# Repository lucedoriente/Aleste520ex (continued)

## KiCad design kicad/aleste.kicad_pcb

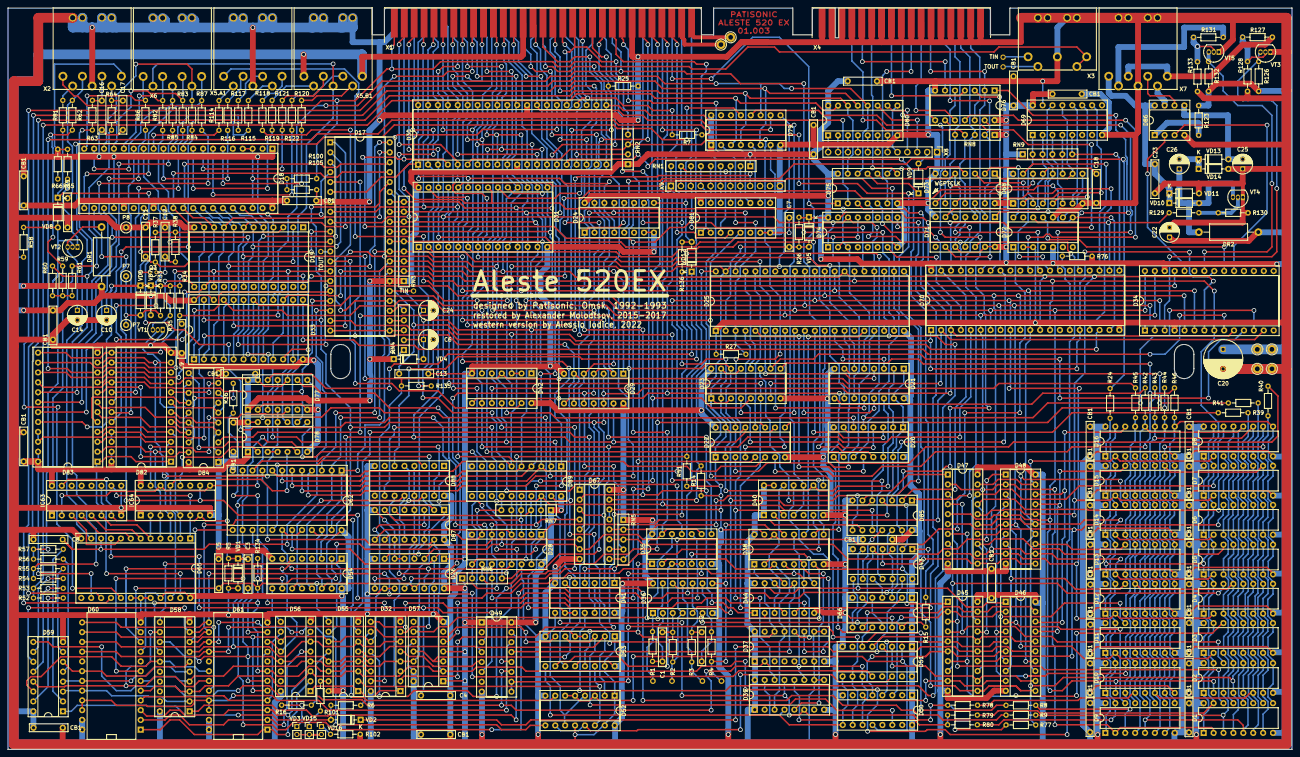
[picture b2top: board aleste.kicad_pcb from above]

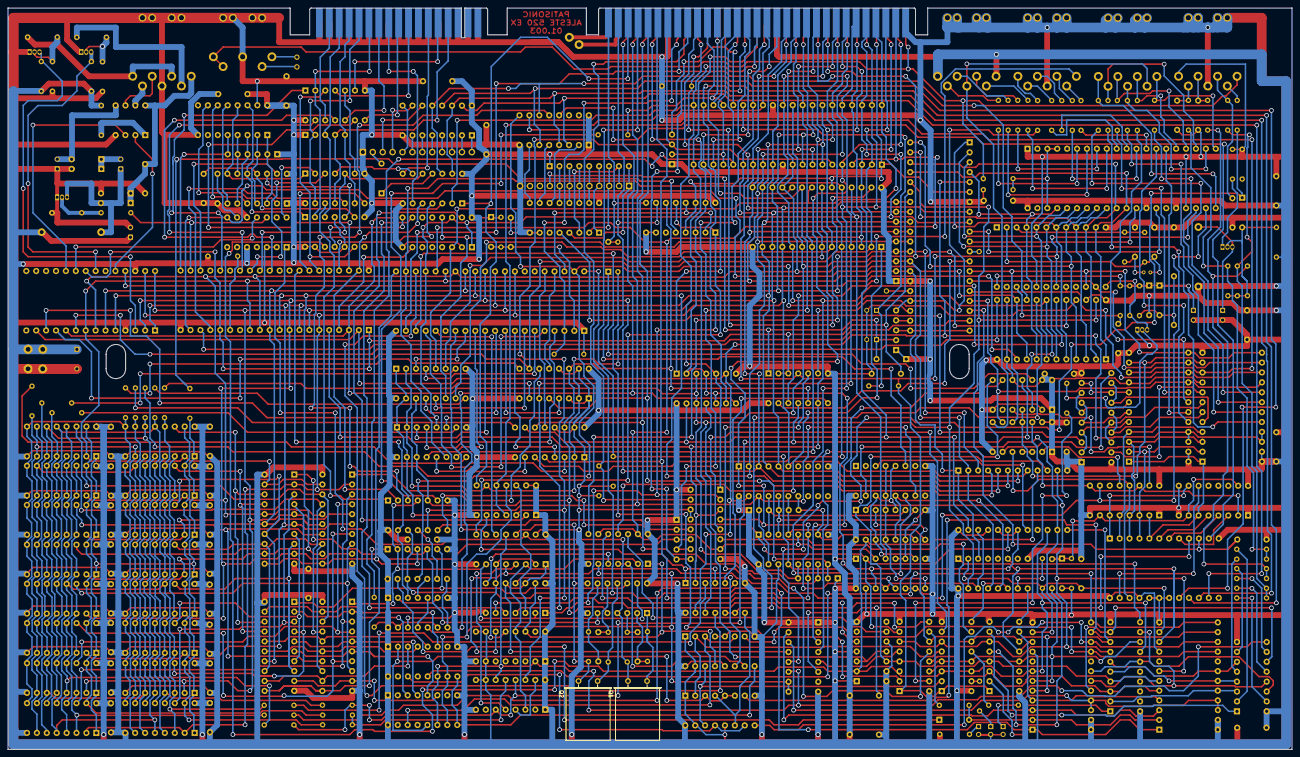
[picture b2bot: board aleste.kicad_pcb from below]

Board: 2 copper layers, 329.2 x 190.1 mm, 279 parts (2 on the bottom side), 452 nets.

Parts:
C1, C2: 470; C_Disc_D7.5_P2.5
C3, C4, C5, C15, C16, C17, C18: CAP; C_Disc_D7.5_P2.5
C6, C24: 1мк; C_Radial_D5_L6_P2.5
C7: 0,33мк; C_Disc_D7.5_P2.5
C8: 1н; C_Disc_D7.5_P2.5
C9: 1,5мк; C_Disc_D7.5_P2.5
C10, C14, C22: 100мк; C_Radial_D5_L6_P2.5
C11: 12; C_Disc_D7.5_P2.5
C12: 24; C_Disc_D7.5_P2.5
C13: 47н; C_Disc_D7.5_P2.5
C20: 1000мк; C_Radial_D10_L16_P5
C23: 0,47мк; C_Disc_D7.5_P2.5
C25, C26: 47мк; C_Radial_D5_L6_P2.5
CB1, CB1#2, CB1#3, CB1#4, CB1#5, CB1#6, CB1#7, CB1#8, CB1#9, CB1#10, CB1#11, CB1#12, CB1#13, CB1#14, CB1#15, CB1#16, CB1#17, CB1#18, CB1#19, CB1#20, CB1#21, CB1#22, CB1#23, CB1#24, CB1#25, CB1#26, CB1#27, CB1#28, CB1#29, CB1#30: 0,1мк; C_Disc_D7.5_P2.5
D1, D2, D3, D4, D5, D6, D7, D8, D9, D10, D11, D12, D13, D14, D15, D16: HM50256P-20; DIP-16_W7.62mm
D17: 8255; DIP-40_W15.24mm_Socket
D18: AY-3-8910; DIP-40_W15.24mm_Socket
D19: MC146818; DIP-24_W15.24mm_Socket
D20, D21, D22, D23, D52, D53: 74LS153; DIP-16_W7.62mm_Socket
D24, D81: 74LS151; DIP-16_W7.62mm_Socket
D25: MC6845P; DIP-40_W15.24mm_Socket
D26: 74LS253; DIP-16_W7.62mm_Socket
D28, D67: AM27S20; DIP-16_W7.62mm_Socket
D29, D44: 74LS32; DIP-14_W7.62mm_Socket
D30: Z80; DIP-40_W15.24mm_Socket
D31: 27512; DIP-28_W15.24mm_Socket
D32, D55, D56, D59, D68, D79: 74LS174; DIP-16_W7.62mm_Socket
D33: 8253; DIP-24_W15.24mm_Socket
D34: 8251A; DIP-28_W15.24mm_Socket
D35, D85: 74LS08; DIP-14_W7.62mm_Socket
D36, D42, D73: 74LS04; DIP-14_W7.62mm_Socket
D37: 74LS161; DIP-16_W7.62mm_Socket
D38: 74LS257; DIP-16_W7.62mm_Socket
D39, D49, D50, D51: 74LS194; DIP-16_W7.62mm_Socket
D40, D57, D66, D71, D77: 74LS74; DIP-14_W7.62mm_Socket
D41, D75, D78: 74LS00; DIP-14_W7.62mm_Socket
D43: 74LS33; DIP-14_W7.62mm_Socket
D45, D46, D47, D48: 74LS373; DIP-20_W7.62mm_Socket
D54, D74: 74LS155; DIP-16_W7.62mm_Socket
D58, D84: 74LS374; DIP-20_W7.62mm_Socket
D60, D61: 1802ИР1; DIP-24
D62, D65: 2716; DIP-24_W15.24mm_Socket
D69: 27S18; DIP-16_W7.62mm_Socket
D70: UPD765AC; DIP-40_W15.24mm_Socket
D72: 74LS93; DIP-14_W7.62mm_Socket
D76: 74LS05; DIP-14_W7.62mm_Socket
D80: 74LS145; DIP-16_W7.62mm_Socket
D82, D83: 1802ИР1; DIP-24_W15.24mm_Socket
D86: SN75150; DIP-8_W7.62mm_Socket
D87, D88: 74LS170; DIP-16_W7.62mm_Socket
D89: 74LS245; DIP-20_W7.62mm_Socket
DR1: 91мкГ; L_Axial_L9.5mm_D4.0mm_P15.24mm_Horizontal_Fastron_SMCC
DR2: 51мкГ; L_Axial_L9.5mm_D4.0mm_P15.24mm_Horizontal_Fastron_SMCC
IC63, IC64: MC14520BDP; DIP-16_W7.62mm_Socket
P1, P2, P3, P4, P5, P6, P7, P7#2, P8: PIN
Q1: 16 MHz; Crystal_HC49-U_Horizontal
Q2: 13.333 MHz; Crystal_HC49-U_Horizontal
Q3: QUARTZ; Crystal_DS15_D1.5mm_L5.0mm_Vertical
R1, R2, R3, R4, R36, R51, R60, R100, R105: 1,2к; R_Axial_DIN0204_L3.6mm_D1.6mm_P7.62mm_Horizontal
R5, R6, R14, R15, R25, R76, R82, R83, R84, R85, R86, R87, R123, R126, R132: 2,7к; R_Axial_DIN0204_L3.6mm_D1.6mm_P7.62mm_Horizontal
R7, R8, R9, R24, R39, R40, R41, R42, R43, R44, R45, R46, R77, R78, R79, R80: 51; R_Axial_DIN0204_L3.6mm_D1.6mm_P7.62mm_Horizontal
R16, R53, R55, R57, R101, R102, R134: 360; R_Axial_DIN0204_L3.6mm_D1.6mm_P7.62mm_Horizontal
R26, R34: 10k; R_Axial_DIN0204_L3.6mm_D1.6mm_P7.62mm_Horizontal
R27, R33, R135: 10к; R_Axial_DIN0204_L3.6mm_D1.6mm_P7.62mm_Horizontal
R35: 390к; R_Axial_DIN0204_L3.6mm_D1.6mm_P7.62mm_Horizontal
R37: 10М; R_Axial_DIN0204_L3.6mm_D1.6mm_P7.62mm_Horizontal
R38: 470к; R_Axial_DIN0204_L3.6mm_D1.6mm_P7.62mm_Horizontal
R52, R54, R56: 200; R_Axial_DIN0204_L3.6mm_D1.6mm_P7.62mm_Horizontal
R58, R129: 510; R_Axial_DIN0204_L3.6mm_D1.6mm_P7.62mm_Horizontal
R59, R127, R131: 6,8к; R_Axial_DIN0204_L3.6mm_D1.6mm_P7.62mm_Horizontal
R61, R128, R133: 3,3к; R_Axial_DIN0204_L3.6mm_D1.6mm_P7.62mm_Horizontal
R62, R63, R64, R66, R81, R130: 220; R_Axial_DIN0204_L3.6mm_D1.6mm_P7.62mm_Horizontal
R65: 120; R_Axial_DIN0204_L3.6mm_D1.6mm_P7.62mm_Horizontal
R114, R115, R116, R117, R118, R119, R120, R121, R122: 27; R_Axial_DIN0204_L3.6mm_D1.6mm_P7.62mm_Horizontal
R136: RES; R_Axial_DIN0204_L3.6mm_D1.6mm_P7.62mm_Horizontal
RN1, RN3: 10k; R_Array_SIP9
RN2: 10k; R_Array_SIP4
RN4: 10k; R_Array_SIP5
RN5, RN6: 1.2k; R_Array_SIP5
RN7, RN9: 1.2k; R_Array_SIP6
RN8: 2,7k; R_Array_SIP5
VD1, VD2, VD4, VD5, VD6, VD7, VD8, VD9, VD10, VD12, VD13, VD14: Diode; D_DO-35_SOD27_P7.62mm_Horizontal
VD3: DA; PinHeader_1x02_P2.00mm_Vertical
VD11: ZDiode; D_DO-35_SOD27_P7.62mm_Horizontal
VD15: CAPS; PinHeader_1x02_P2.00mm_Vertical
VD16: PWR; PinHeader_1x02_P2.00mm_Vertical
VT1, VT2, VT3, VT4, VT5: NPN; TO-92_Inline
X1: SLOT-62; SLOT_62
X2, X5.A1, X5.B1, X6, X7: CONN-7S; DNR-8F1R
X3: CONN-5S; DNR-5F1R
X4: SLOT-34
X8, X9: CONN-12; PinHeader_1x12_P2.54mm_Vertical

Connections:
/1CY: D78.2, IC64.12 (Q1B)
/1M: D18.22 (CLOCK), D37.11 (Q3), D38.5 (I0b), IC64.10 (EB)
/2CY: D65.22 (A9), D78.5, IC64.13 (Q2B)
/2M: D37.12 (Q2), D38.2 (I0a), D38.6 (I1b), D44.9
/3CY: D78.12, IC63.2 (EA), IC64.9 (CB), IC64.14 (Q3B)
/4M: D35.2, D37.13 (Q1), D38.3 (I1a), D39.3 (P0)
/8M: D35.1, D37.14 (Q0), D44.13, D53.13 (I3b)
/16MHZ: D36.4, D38.14 (I0c), D72.1 (CP1..3), Q1.1, R2.2
/A0: D30.30 (A0), D31.10 (A0), D33.19 (A0), D41.2, D42.9, D67.3 (A4), D70.5 (A0), X1.B9
/A1: D20.6 (I0a), D30.31 (A1), D31.9 (A1), D33.20 (A1), X1.A9
/A2: D20.10 (I0b), D30.32 (A2), D31.8 (A2), X1.B8
/A3: D21.6 (I0a), D30.33 (A3), D31.7 (A3), X1.A8
/A4: D21.10 (I0b), D30.34 (A4), D31.6 (A4), X1.B7
/A5: D22.6 (I0a), D30.35 (A5), D31.5 (A5), X1.A7
/A6: D23.6 (I0a), D30.36 (A6), D31.4 (A6), D44.4, X1.B6
/A7: D21.11 (I1b), D30.37 (A7), D31.3 (A7), D74.13 (A0), X1.A6
/A8: D17.9 (A0), D20.5 (I1a), D25.24 (RS), D26.4 (I2a), D30.38 (A8), D31.25 (A8), D34.12 (C/D), D74.1 (Ea1), D74.14 (Eb1), X1.B5
/A9: D17.8 (A1), D20.11 (I1b), D25.22 (R/~W), D26.12 (I2b), D30.39 (A9), D31.24 (A9), X1.A5
/A10: D21.5 (I1a), D30.40 (A10), D31.21 (A10), D74.3 (A1), X1.B4
/A11: D17.6 (~CS), D24.4 (I0), D24.14 (I5), D30.1 (A11), D31.23 (A11), X1.A4
/A12: D23.10 (I0b), D30.2 (A12), D31.2 (A12), D34.11 (CS), X1.B3
/A13: D22.10 (I0b), D29.13, D30.3 (A13), D31.26 (A13), D62.23 (A8), X1.A3
/A14: D25.25 (~CS), D26.3 (I3a), D28.5 (A0), D30.4 (A14), D35.9, D35.13, D67.7 (A2), X1.B2
/A15: D26.13 (I3b), D28.6 (A1), D30.5 (A15), D54.14 (Eb1), D62.22 (A9), D67.4 (A3), D89.1 (A->B), X1.A2
/AGND: P4.1, X1.A30
/AVCC: P3.1, X1.A31
/BUFFER0: D47.1 (OE), D67.12 (O0), RN5.2 (R1.2)
/BUFFER1: D48.1 (OE), D67.11 (O1), RN5.3 (R2.2)
/CAS: D39.12 (Q3), R79.1, R80.1
/CBUF: D25.21 (CLK), D43.4, D47.11 (LE), D48.11 (LE)
/CLK: D30.6 (~CLK), D39.14 (Q1), D40.3 (C), RN2.3 (R2), X1.B25
/CPU/LOP: D43.10, D66.4 (~S)
/CPU/~RESET*: C24.1, D30.26 (~RESET), R135.2
/CS53: D32.12 (Q4), D42.5
/CURSOR: D25.19 (CURSOR), D33.16 (G2), X1.B23
/Clocks & CRTC/13MHZ: D36.8, D38.13 (I1c), Q2.1, R4.2
/Clocks & CRTC/V11: D25.14 (MA10), D38.10 (I1d)
/Clocks & CRTC/V13: D25.16 (MA12), D38.11 (I0d)
/Clocks & CRTC/~RESET2: C7.2, D25.2 (~RESET), R26.1, VD5.2 (A)
/D0: D1.2 (DIN), D9.2 (DIN), D17.34 (D0), D25.33 (D0), D30.14 (D0), D31.11 (D0), D34.27 (D0), D47.2 (O0), D48.2 (O0), D62.8 (A0), D70.6 (DB0), D89.6 (A4), RN3.9 (R8), X1.B13
/D1: D2.2 (DIN), D10.2 (DIN), D17.33 (D1), D25.32 (D1), D30.15 (D1), D31.12 (D1), D34.28 (D1), D47.5 (O1), D48.5 (O1), D62.7 (A1), D70.7 (DB1), D89.5 (A3), RN3.8 (R7), X1.A13
/D2: D3.2 (DIN), D11.2 (DIN), D17.32 (D2), D25.31 (D2), D30.12 (D2), D31.13 (D2), D34.1 (D2), D47.6 (O2), D48.6 (O2), D62.6 (A2), D70.8 (DB2), D89.4 (A2), RN3.7 (R6), X1.B12
/D3: D4.2 (DIN), D12.2 (DIN), D17.31 (D3), D25.30 (D3), D30.8 (D3), D31.15 (D3), D34.2 (D3), D47.9 (O3), D48.9 (O3), D62.5 (A3), D70.9 (DB3), D89.3 (A1), RN3.6 (R5), X1.A12
/D4: D5.2 (DIN), D13.2 (DIN), D17.30 (D4), D25.29 (D4), D30.7 (D4), D31.16 (D4), D34.5 (D4), D47.12 (O4), D48.12 (O4), D62.4 (A4), D70.10 (DB4), D89.2 (A0), RN3.5 (R4), X1.B11
/D5: D6.2 (DIN), D14.2 (DIN), D17.29 (D5), D25.28 (D5), D30.9 (D5), D31.17 (D5), D34.6 (D5), D47.15 (O5), D48.15 (O5), D62.3 (A5), D70.11 (DB5), RN3.4 (R3), X1.A11
/D6: D7.2 (DIN), D15.2 (DIN), D17.28 (D6), D25.27 (D6), D30.10 (D6), D31.18 (D6), D34.7 (D6), D47.16 (O6), D48.16 (O6), D54.13 (A0), D62.2 (A6), D70.12 (DB6), RN3.3 (R2), X1.B10
/D7: D8.2 (DIN), D16.2 (DIN), D17.27 (D7), D25.26 (D7), D30.13 (D7), D31.19 (D7), D34.8 (D7), D47.19 (O7), D48.19 (O7), D54.3 (A1), D62.1 (A7), D70.13 (DB7), RN3.2 (R1), X1.A10
/DEN: D25.18 (DE), D77.12 (D)
/DIS: D20.2 (S1), D21.2 (S1), D22.2 (S1), D23.2 (S1), D24.10 (S1), D40.9 (Q), X1.B30
/DISCINT: D17.19 (PB1), D70.18 (INT)
/DW: D70.22 (RDW), D72.12 (Q0), R129.1
/EXRG: D44.5, D74.10 (Q1b)
/FDC/DSKRDY: D70.35 (RDY), D71.9 (Q), D76.3
/FDC/FP0: D68.3 (D0), D69.1 (Q0), RN9.2 (R1)
/FDC/FP1: D68.4 (D1), D69.2 (Q1), RN9.3 (R2)
/FDC/FP2: D68.6 (D2), D69.3 (Q2), RN9.4 (R3)
/FDC/FP3: D68.11 (D3), D69.4 (Q3), RN9.5 (R4)
/FDC/RDD: D68.15 (Q5), D70.23 (RD)
/FDC/RW/S: D70.39 (~RW/SEEK), D75.5, D85.2
/FDC/WRC: D69.5 (Q4), D70.21 (WCK), RN9.6 (R5)
/FDC/~DIR: D76.8, X4.A9
/FDC/~DRIVE0: D76.6, X4.A5
/FDC/~DRIVE1: D75.8, X4.A6
/FDC/~GATE: D71.2 (D), D76.2, X4.A12
/FDC/~INDEX: D73.11, RN8.4 (R3.2), X4.A4
/FDC/~MOTOR: D76.4, X4.A8
/FDC/~RDATA: D71.3 (C), RN8.3 (R2.2), X4.A15
/FDC/~SIDE: D76.12, X4.A16
/FDC/~STEP: D75.6, X4.A10
/FDC/~TRAC0: D73.13, RN8.2 (R1.2), X4.A13
/FDC/~WRDAT: D76.10, X4.A11
/FDC/~WRTPRT: D73.9, RN8.5 (R4.2), X4.A14
/Gate Array/4ST: D35.3, D35.4, D53.10 (I0b)
/Gate Array/8ST: D44.11, D53.11 (I1b)
/Gate Array/"A": D26.7 (Za), D87.5 (Ra), D87.14 (Wa), D88.5 (Ra), D88.14 (Wa)
/Gate Array/"B": D26.9 (Zb), D87.4 (Rb), D87.13 (Wb), D88.4 (Rb), D88.13 (Wb)
/Gate Array/B: C15.1, R62.1, X2.4
/Gate Array/BLAKS: D32.10 (Q3), R6.2
/Gate Array/BLANK: D59.1 (~Mr), R6.1, VD2.2 (A)
/Gate Array/C0: D58.2 (O0), D59.3 (D0), D60.20 (DB0)
/Gate Array/C1: D58.5 (O1), D59.4 (D1), D60.19 (DB1)
/Gate Array/C2: D58.6 (O2), D59.6 (D2), D60.18 (DB2)
/Gate Array/C3: D58.9 (O3), D59.11 (D3), D61.20 (DB0)
/Gate Array/C4: D58.12 (O4), D59.13 (D4), D61.19 (DB1)
/Gate Array/C5: D58.15 (O5), D59.14 (D5), D61.18 (DB2)
/Gate Array/CBORDER: D54.6 (Q1a), D58.11 (Cp)
/Gate Array/COLOR: C5.2, D54.2 (Ea2), D60.11 (~WA), D61.11 (~WA), R134.1
/Gate Array/G: C16.1, R63.1, X2.5
/Gate Array/HIGHTX: D32.5 (Q1), D49.5 (P2)
/Gate Array/HIGHTY: D32.2 (Q0), R136.2
/Gate Array/LED0: D55.12 (Q4), R16.1
/Gate Array/LED1: D55.15 (Q5), R101.1
/Gate Array/M0: D28.7 (A2), D87.10 (Q1), D89.14 (B4), RN7.6 (R5.2)
/Gate Array/M1: D28.4 (A3), D87.9 (Q2), D89.15 (B3), RN7.5 (R4.2)
/Gate Array/M2: D28.3 (A4), D87.7 (Q3), D89.16 (B2), RN7.4 (R3.2)
/Gate Array/M3: D28.2 (A5), D87.6 (Q4), D89.17 (B1), RN7.3 (R2.2)
/Gate Array/MAPER: D54.12 (Q3b), D87.12 (~Ew), D88.12 (~Ew)
/Gate Array/MAPMOD: D26.2 (A1), D28.1 (A6), D32.7 (Q2), D62.19 (A10), D85.9
/Gate Array/MODE: D54.11 (Q2b), D55.9 (Cp)
/Gate Array/MODE0: D52.14 (S0), D53.14 (S0), D55.2 (Q0)
/Gate Array/MODE1: D52.2 (S1), D53.2 (S1), D55.5 (Q1)
/Gate Array/NCOLOR: D54.9 (Q0b), D56.9 (Cp)
/Gate Array/NCOLOR0: D56.2 (Q0), D60.1 (AA0), D61.1 (AA0)
/Gate Array/NCOLOR1: D56.5 (Q1), D60.2 (AA1), D61.2 (AA1)
/Gate Array/NCOLOR2: D56.7 (Q2), D60.3 (AA2), D61.3 (AA2)
/Gate Array/NCOLOR3: D56.10 (Q3), D60.4 (AA3), D61.4 (AA3)
/Gate Array/NCOLOR4: D54.1 (Ea1), D56.12 (Q4), D60.10 (~ECA), D61.10 (~ECA)
/Gate Array/PAGE: D49.15 (Q0), D58.1 (OE)
/Gate Array/PX0: D51.12 (Q3), D60.13 (AB0), D61.13 (AB0)
/Gate Array/PX1: D52.7 (Za), D60.14 (AB1), D61.14 (AB1)
/Gate Array/PX2: D52.9 (Zb), D60.15 (AB2), D61.15 (AB2)
/Gate Array/PX3: D53.7 (Za), D60.16 (AB3), D61.16 (AB3)
/Gate Array/R: C17.1, R64.1, X2.3
/Gate Array/RRC: D50.9 (S0), D51.9 (S0), D53.9 (Zb)
/Gate Array/SYNC: D49.12 (Q3), R81.1, VD8.1 (K)
/Gate Array/VRAMACC: D62.17 (Q7), D88.3 (D4)
/Gate Array/XD1: D32.4 (D1), D55.4 (D1), D56.4 (D1), D57.12 (D), D58.4 (D1), D60.6 (DA1), D62.10 (Q1), D87.1 (D2)
/Gate Array/XD2: D32.6 (D2), D55.6 (D2), D56.6 (D2), D58.7 (D2), D60.7 (DA2), D62.11 (Q2), D87.2 (D3)
/Gate Array/XD3: D32.11 (D3), D55.11 (D3), D56.11 (D3), D58.8 (D3), D61.5 (DAO), D62.13 (Q3), D87.3 (D4)
/Gate Array/XD4: D32.13 (D4), D55.13 (D4), D56.13 (D4), D58.13 (D4), D61.6 (DA1), D62.14 (Q4), D88.15 (D1)
/Gate Array/XD5: D32.14 (D5), D55.14 (D5), D58.14 (D5), D61.7 (DA2), D62.15 (Q5)
/Gate Array/~PAGE: D49.14 (Q1), D60.21 (~RB), D60.22 (~ECB), D61.21 (~RB), D61.22 (~ECB)
/HIGHT: D38.1 (S), D44.10, D44.12, D49.13 (Q2)
/HIGHTZ: D24.9 (S2), R136.1, VD12.2 (A), X1.B31
/HX: D25.39 (HS), D33.18 (CLK2), D43.11, D77.3 (C), D79.9 (Cp)
/HY: C3.1, D25.40 (VS), D43.12, D85.12
/HY*: C8.1, D17.18 (PB0), D65.10 (Q1)
/KK0: D65.14 (Q4), D79.3 (D0), D80.15 (P0)
/KK1: D65.15 (Q5), D75.13, D79.4 (D1), D80.14 (P1)
/KK2: D65.16 (Q6), D79.6 (D2), D80.13 (P2)
/KK3: D65.17 (Q7), D75.12, D79.11 (D3), D80.12 (P3)
/L0: D24.2 (I2), D24.13 (I6), D25.38 (RA0)
/L1: D23.12 (I2b), D25.37 (RA1)
/L2: D22.12 (I2b), D25.36 (RA2)
/L.PEN: D25.3 (LPSTB), R27.2, X1.A24
/M4: D28.15 (A7), D85.10, D88.10 (Q1), D89.18 (B0), RN7.2 (R1.2), X1.A28
/MAP14: D24.3 (I1), D24.15 (I4), D28.12 (O0), RN6.5 (R4.2), X1.A26
/MAP15: D22.5 (I1a), D28.11 (O1), RN6.4 (R3.2), X1.B26
/MAP16: D22.11 (I1b), D28.10 (O2), RN6.3 (R2.2), X1.A27
/MAP17: D23.5 (I1a), D28.9 (O3), RN6.2 (R1.2), X1.B27
/MAP18: D23.11 (I1b), D85.8
/MAPBLK: D28.13 (CS1), D88.11 (~Er), R51.2, X1.B28
/MK0: D65.5 (A3), D82.1 (AA0), D83.1 (AA0), IC63.6 (Q3A), IC64.2 (EA)
/MK1: D65.4 (A4), D82.2 (AA1), D83.2 (AA1), IC64.3 (Q0A)
/MK2: D65.3 (A5), D82.3 (AA2), D83.3 (AA2), IC64.4 (Q1A)
/MK3: D65.2 (A6), D82.4 (AA3), D83.4 (AA3), IC64.5 (Q2A)
/MVI: D35.6, D40.11 (C), D49.9 (S0), D49.10 (S1), D50.10 (S1), D51.10 (S1)
/PROM0: D55.7 (Q2), D67.5 (A0)
/PROM1: D55.10 (Q3), D67.6 (A1)
/Periphery/50/60: D17.22 (PB4), RN4.4 (R3.2)
/Periphery/+12V: C23.2, D86.8 (VCC+), VD10.1 (K), VD11.1 (K), X7.6
/Periphery/-12V: C25.2, D86.5 (VCC-), VD13.2 (A)
/Periphery/AY0: D17.4 (PA0), D18.37 (DA0), D19.4 (AD0), D33.8 (D0)
/Periphery/AY1: D17.3 (PA1), D18.36 (DA1), D19.5 (AD1), D33.7 (D1)
/Periphery/AY2: D17.2 (PA2), D18.35 (DA2), D19.6 (AD2), D33.6 (D2)
/Periphery/AY3: D17.1 (PA3), D18.34 (DA3), D19.7 (AD3), D33.5 (D3)
/Periphery/AY4: D17.40 (PA4), D18.33 (DA4), D19.8 (AD4), D33.4 (D4)
/Periphery/AY5: D17.39 (PA5), D18.32 (DA5), D19.9 (AD5), D33.3 (D5)
/Periphery/AY6: D17.38 (PA6), D18.31 (DA6), D19.10 (AD6), D33.2 (D6)
/Periphery/AY7: D17.37 (PA7), D18.30 (DA7), D19.11 (AD7), D33.1 (D7)
/Periphery/BC1: D17.11 (PC6), D18.29 (BC1)
/Periphery/BDIR: D17.10 (PC7), D18.27 (BDIR)
/Periphery/BUSY: D17.24 (PB6), R118.1, RN4.5 (R4.2)
/Periphery/COMMON: D78.8, X5.B1.2, X6.1
/Periphery/DSR: D34.22 (DSR), R132.2, VT5.3 (C)
/Periphery/DSR*: R131.1, X7.1
/Periphery/DTR: D34.24 (DTR), D86.2 (1A)
/Periphery/DTR*: D86.7 (1Y), X7.3
/Periphery/FUTURE: D33.17 (OUT2), D41.9, D41.10
/Periphery/KM0: D80.1 (Q0), X8.12
/Periphery/KM1: D80.2 (Q1), X8.11
/Periphery/KM2: D80.3 (Q2), X8.10
/Periphery/KM3: D80.4 (Q3), X8.9
/Periphery/KM4: D80.5 (Q4), X8.8
/Periphery/KM5: D80.6 (Q5), X8.7
/Periphery/KM6: D80.7 (Q6), X8.6
/Periphery/KM7: D80.9 (Q7), X8.5
/Periphery/KM8: D80.10 (Q8), X8.4
/Periphery/KM9: D80.11 (Q9), X8.3
/Periphery/KM10: VD9.2 (A), X8.2
/Periphery/KM11: D81.4 (I0), RN1.9 (R8), X9.1
/Periphery/KM12: D81.3 (I1), RN1.8 (R7), X9.2
/Periphery/KM13: D81.2 (I2), RN1.7 (R6), X9.3
/Periphery/KM14: D81.1 (I3), RN1.6 (R5), X9.4
/Periphery/KM15: D81.15 (I4), RN1.5 (R4), X9.5
/Periphery/KM16: D81.14 (I5), RN1.4 (R3), X9.6
/Periphery/KM17: D81.13 (I6), RN1.3 (R2), X9.7
/Periphery/KM18: D81.12 (I7), RN1.2 (R1), X9.8
/Periphery/KRS: D81.5 (Z), D84.3 (D0)
/Periphery/KW0: D79.2 (Q0), D81.11 (S0)
/Periphery/KW1: D79.5 (Q1), D81.10 (S1)
/Periphery/KW2: D79.7 (Q2), D81.9 (S2)
/Periphery/KW3: D79.10 (Q3), D82.10 (~ECA), D83.10 (~ECA)
/Periphery/PB2: D17.20 (PB2), D17.21 (PB3), RN4.3 (R2.2)
/Periphery/PD0: D18.13 (IOB0), R114.1
/Periphery/PD1: D18.12 (IOB1), R116.1
/Periphery/PD2: D18.11 (IOB2), R117.1
/Periphery/PD3: D18.10 (IOB3), R115.1
/Periphery/PD4: D18.9 (IOB4), R119.1
/Periphery/PD5: D18.8 (IOB5), R121.1
/Periphery/PD6: D18.7 (IOB6), R122.1
/Periphery/PD7: D18.6 (IOB7), R120.1
/Periphery/RXC: D33.10 (OUT0), D34.25 (RXC)
/Periphery/RXD: D34.3 (RXD), R126.1, VT3.3 (C)
/Periphery/SABC: D18.3 (ANALOG_B), D18.4 (ANALOG_A), D18.38 (ANALOG_C), R100.1, R105.2
/Periphery/SBRES: C6.1, D42.1, RN4.2 (R1.2), VD4.2, X9.9
/Periphery/STROBE: D17.13 (PC4), D42.13
/Periphery/TIN: D17.25 (PB7), X3.1
/Periphery/TOUT: D17.12 (PC5), X3.4
/Periphery/TXC: D33.13 (OUT1), D34.9 (TXC)
/Periphery/TXD: D34.19 (TXD), D86.3 (2A)
/Periphery/TXD*: D86.6 (2Y), X7.5
/Periphery/VC1: C10.1, D19.24 (VDD), R33.1, R34.2, R35.2, VD6.1 (K), VD7.1 (K)
/Periphery/X1: D18.21 (IOA0), R87.2, X6.7
/Periphery/X2: D18.20 (IOA1), R86.2, X6.6
/Periphery/X3: D18.19 (IOA2), R85.2, X6.2
/Periphery/X4: D18.18 (IOA3), R84.2, X6.3
/Periphery/X5: D18.17 (IOA4), R83.2, X6.5
/Periphery/X6: D18.16 (IOA5), R82.2, X6.4
/Periphery/X7: D18.15 (IOA6), D82.19 (DB1)
/Periphery/X8: D18.14 (IOA7), D82.20 (DB0)
/Periphery/Y0: D17.14 (PC0), D19.15 (R/W), D78.10, D82.13 (AB0), D83.13 (AB0)
/Periphery/Y1: D17.15 (PC1), D19.14 (AS), D82.14 (AB1), D83.14 (AB1)
/Periphery/Y2: D17.16 (PC2), D19.17 (DS), D82.15 (AB2), D83.15 (AB2)
/Periphery/Y3: D17.17 (PC3), D78.9, D82.16 (AB3), D83.16 (AB3)
/Periphery/Z0: D82.5 (DAO), D84.2 (O0), D84.4 (D1)
/Periphery/Z1: D82.6 (DA1), D84.5 (O1), D84.7 (D2)
/Periphery/Z2: D82.7 (DA2), D84.6 (O2), D84.8 (D3)
/Periphery/Z3: D82.8 (DA3), D84.9 (O3), D84.13 (D4)
/Periphery/Z4: D83.5 (DAO), D84.12 (O4), D84.14 (D5)
/Periphery/Z5: D83.6 (DA1), D84.15 (O5), D84.17 (D6)
/Periphery/Z6: D83.7 (DA2), D84.16 (O6), D84.18 (D7)
/Periphery/Z7: D83.8 (DA3), D84.19 (O7)
/Periphery/~CS53: D33.21 (~CS), D42.6
/Periphery/~STROBE: D42.12, X5.A1.6
/RAM/CAS0: D1.15 (CAS), D2.15 (CAS), D3.15 (CAS), D4.15 (CAS), D5.15 (CAS), D6.15 (CAS), D7.15 (CAS), D8.15 (CAS), R79.2
/RAM/CAS1: D9.15 (CAS), D10.15 (CAS), D11.15 (CAS), D12.15 (CAS), D13.15 (CAS), D14.15 (CAS), D15.15 (CAS), D16.15 (CAS), R80.2
/RAM/MA0: D1.5 (A0), D2.5 (A0), D3.5 (A0), D4.5 (A0), D5.5 (A0), D6.5 (A0), D7.5 (A0), D8.5 (A0), D9.5 (A0), D10.5 (A0), D11.5 (A0), D12.5 (A0), D13.5 (A0), D14.5 (A0), D15.5 (A0), D16.5 (A0), R39.2
/RAM/MA1: D1.7 (A1), D2.7 (A1), D3.7 (A1), D4.7 (A1), D5.7 (A1), D6.7 (A1), D7.7 (A1), D8.7 (A1), D9.7 (A1), D10.7 (A1), D11.7 (A1), D12.7 (A1), D13.7 (A1), D14.7 (A1), D15.7 (A1), D16.7 (A1), R40.2
/RAM/MA2: D1.6 (A2), D2.6 (A2), D3.6 (A2), D4.6 (A2), D5.6 (A2), D6.6 (A2), D7.6 (A2), D8.6 (A2), D9.6 (A2), D10.6 (A2), D11.6 (A2), D12.6 (A2), D13.6 (A2), D14.6 (A2), D15.6 (A2), D16.6 (A2), R41.2
/RAM/MA3: D1.12 (A3), D2.12 (A3), D3.12 (A3), D4.12 (A3), D5.12 (A3), D6.12 (A3), D7.12 (A3), D8.12 (A3), D9.12 (A3), D10.12 (A3), D11.12 (A3), D12.12 (A3), D13.12 (A3), D14.12 (A3), D15.12 (A3), D16.12 (A3), R42.2
/RAM/MA4: D1.11 (A4), D2.11 (A4), D3.11 (A4), D4.11 (A4), D5.11 (A4), D6.11 (A4), D7.11 (A4), D8.11 (A4), D9.11 (A4), D10.11 (A4), D11.11 (A4), D12.11 (A4), D13.11 (A4), D14.11 (A4), D15.11 (A4), D16.11 (A4), R43.2
/RAM/MA5: D1.10 (A5_1), D2.10 (A5_1), D3.10 (A5_1), D4.10 (A5_1), D5.10 (A5_1), D6.10 (A5_1), D7.10 (A5_1), D8.10 (A5_1), D9.10 (A5_1), D10.10 (A5_1), D11.10 (A5_1), D12.10 (A5_1), D13.10 (A5_1), D14.10 (A5_1), D15.10 (A5_1), D16.10 (A5_1), R44.2
/RAM/MA6: D1.13 (A5_2), D2.13 (A5_2), D3.13 (A5_2), D4.13 (A5_2), D5.13 (A5_2), D6.13 (A5_2), D7.13 (A5_2), D8.13 (A5_2), D9.13 (A5_2), D10.13 (A5_2), D11.13 (A5_2), D12.13 (A5_2), D13.13 (A5_2), D14.13 (A5_2), D15.13 (A5_2), D16.13 (A5_2), R45.2
/RAM/MA7: D1.9 (A7), D2.9 (A7), D3.9 (A7), D4.9 (A7), D5.9 (A7), D6.9 (A7), D7.9 (A7), D8.9 (A7), D9.9 (A7), D10.9 (A7), D11.9 (A7), D12.9 (A7), D13.9 (A7), D14.9 (A7), D15.9 (A7), D16.9 (A7), R46.2
/RAM/MA8: D1.1 (A8), D2.1 (A8), D3.1 (A8), D4.1 (A8), D5.1 (A8), D6.1 (A8), D7.1 (A8), D8.1 (A8), D9.1 (A8), D10.1 (A8), D11.1 (A8), D12.1 (A8), D13.1 (A8), D14.1 (A8), D15.1 (A8), D16.1 (A8), R24.2
/RAM/R0: D1.14 (DOUT), D45.3 (D0), D47.3 (D0)
/RAM/R1: D2.14 (DOUT), D45.4 (D1), D47.4 (D1)
/RAM/R2: D3.14 (DOUT), D45.7 (D2), D47.7 (D2)
/RAM/R3: D4.14 (DOUT), D45.8 (D3), D47.8 (D3)
/RAM/R4: D5.14 (DOUT), D45.13 (D4), D47.13 (D4)
/RAM/R5: D6.14 (DOUT), D45.14 (D5), D47.14 (D5)
/RAM/R6: D7.14 (DOUT), D45.17 (D6), D47.17 (D6)
/RAM/R7: D8.14 (DOUT), D45.18 (D7), D47.18 (D7)
/RAM/R8: D9.14 (DOUT), D46.3 (D0), D48.3 (D0)
/RAM/R9: D10.14 (DOUT), D46.4 (D1), D48.4 (D1)
/RAM/R10: D11.14 (DOUT), D46.7 (D2), D48.7 (D2)
/RAM/R11: D12.14 (DOUT), D46.8 (D3), D48.8 (D3)
/RAM/R12: D13.14 (DOUT), D46.13 (D4), D48.13 (D4)
/RAM/R13: D14.14 (DOUT), D46.14 (D5), D48.14 (D5)
/RAM/R14: D15.14 (DOUT), D46.17 (D6), D48.17 (D6)
/RAM/R15: D16.14 (DOUT), D46.18 (D7), D48.18 (D7)
/RAM/RAS0: D1.4 (RAS), D2.4 (RAS), D3.4 (RAS), D4.4 (RAS), D5.4 (RAS), D6.4 (RAS), D7.4 (RAS), D8.4 (RAS), R77.2
/RAM/RAS1: D9.4 (RAS), D10.4 (RAS), D11.4 (RAS), D12.4 (RAS), D13.4 (RAS), D14.4 (RAS), D15.4 (RAS), D16.4 (RAS), R78.2
/RAM/S0: D20.14 (S0), D21.14 (S0), D22.14 (S0), D23.14 (S0), D24.11 (S0), D36.5, D42.10, D85.5
/RAM/VBUF: D43.1, D45.11 (LE), D46.11 (LE)
/RAM/WE0: D1.3 (WE), D2.3 (WE), D3.3 (WE), D4.3 (WE), D5.3 (WE), D6.3 (WE), D7.3 (WE), D8.3 (WE), R9.2
/RAM/WE1: D9.3 (WE), D10.3 (WE), D11.3 (WE), D12.3 (WE), D13.3 (WE), D14.3 (WE), D15.3 (WE), D16.3 (WE), R8.2
/RAM/~VCLK: D36.12, D43.6, D46.1 (OE)
/RAMDIS: D67.15 (A7), R14.2, X1.A23
/RAS: D39.6 (P3), D39.13 (Q2), D42.11, D77.11 (C), R77.1, R78.1
/RESET: C13.2, D17.35 (RESET), D34.21 (RESET), D42.2, D42.3, D70.1 (RESET), D70.16 (TC)
/ROM0: D35.10, D57.5 (Q)
/ROM1: D35.12, D57.9 (Q)
/ROMDIS: D31.22 (~OE), R25.1, X1.A22
/RSCLK: D34.20 (CLK), D72.11 (Q3)
/SINT: D66.3 (C), D79.12 (Q4), D85.13
/SINT*: D65.11 (Q2), D79.13 (D4)
/SOUND: R100.2, X1.A1, X2.6, X3.3, X3.5
/SYNC*: C4.2, D49.6 (P3), D65.9 (Q0)
/V1: D20.4 (I2a), D25.4 (MA0)
/V2: D20.12 (I2b), D25.5 (MA1)
/V3: D21.4 (I2a), D25.6 (MA2)
/V4: D21.12 (I2b), D25.7 (MA3)
/V5: D22.4 (I2a), D25.8 (MA4)
/V6: D23.4 (I2a), D25.9 (MA5)
/V7: D21.13 (I3b), D25.10 (MA6)
/V8: D20.3 (I3a), D25.11 (MA7)
/V9: D20.13 (I3b), D25.12 (MA8)
/V10: D21.3 (I3a), D25.13 (MA9)
/V14: D22.3 (I3a), D25.17 (MA13)
/V1113: D24.1 (I3), D24.12 (I7), D38.9 (Zd)
/VCLK: D36.13, D38.7 (Zb), D43.2, D44.2, D45.1 (OE), D85.4
/VD0: D45.2 (O0), D46.2 (O0), D50.3 (P0)
/VD1: D45.5 (O1), D46.5 (O1), D50.4 (P1)
/VD2: D45.6 (O2), D46.6 (O2), D50.5 (P2)
/VD3: D45.9 (O3), D46.9 (O3), D50.6 (P3)
/VD4: D45.12 (O4), D46.12 (O4), D51.3 (P0)
/VD5: D45.15 (O5), D46.15 (O5), D51.4 (P1)
/VD6: D45.16 (O6), D46.16 (O6), D51.5 (P2)
/VD7: D45.19 (O7), D46.19 (O7), D51.6 (P3)
/WGPTCLK: D33.9 (CLK0), D33.15 (CLK1), D70.19 (CLK), D72.8 (Q2)
/XD0: D32.3 (D0), D55.3 (D0), D56.3 (D0), D57.2 (D), D58.3 (D0), D60.5 (DAO), D62.9 (Q0), D71.12 (D), D87.15 (D1)
/XTAL: D37.2 (CP), D38.12 (Zc), D39.11 (Cp), D49.11 (Cp), D50.11 (Cp), D51.11 (Cp), D59.9 (Cp)
/~3CY: D77.4 (~S), D78.11, D82.11 (~WA), D83.11 (~WA)
/~BUSAK: D30.23 (~BUSACK), X1.B19
/~BUSRQ: D30.25 (~BUSRQ), RN2.4 (R3), X1.A19
/~CSAY: D32.15 (Q5), R36.1
/~DIS: D40.8 (~Q), D75.1, X1.B29
/~FUTURE: D41.8, D52.4 (I2a), D52.11 (I1b)
/~HALT: D30.18 (~HALT), X1.B17
/~INTA: D29.8, D66.10 (~S), X1.A29
/~INT: D30.16 (~INT), R15.2, X1.A18
/~IORD: D17.5 (~RD), D29.6, D34.13 (RD), D41.13, D70.2 (~RD), D82.21 (~RB), D82.22 (~ECB), D83.21 (~RB), D83.22 (~ECB), D89.19 (CE)
/~IORQ: D26.14 (A0), D29.2, D29.4, D29.10, D30.20 (~IORQ), D62.18 (~EP), D62.20 (~G), X1.A16
/~IOWR: D17.36 (~WR), D29.3, D29.12, D33.23 (~WR), D34.10 (WR), D41.12, D54.15 (Eb2), D70.3 (~WR), D74.15 (Eb2)
/~M1: D29.9, D30.27 (~M1), X1.A15
/~MREQ: D30.19 (~MREQ), D44.1, D67.2 (A5), X1.B14
/~NMI: D30.17 (~NMI), RN2.2 (R1), X1.B18
/~RAMEN: D67.9 (O3), RN5.5 (R4.2), X1.B22
/~RD: D29.5, D30.21 (~RD), D67.1 (A6), D75.2, X1.B16
/~RESET: D18.23 (~RESET), D19.18 (RESET), D32.1 (~Mr), D42.4, D55.1 (~Mr), D56.1 (~Mr), R135.1, X1.A21
/~RFSH: D30.28 (~RFSH), D40.4 (~S), D40.10 (~S), X1.B15
/~ROMEN: D31.20 (~CS), D67.10 (O2), RN5.4 (R3.2), X1.B21
/~WAIT: D30.24 (~WAIT), R7.2, X1.A20
/~WR: D29.1, D30.22 (~WR), X1.A17
GND: C4.1, C5.1, C6.2, C7.1, C8.2, C9.1, C10.2, C11.1, C12.1, C13.1, C14.2, C15.2, C16.2, C17.2, C18.1, C20.2, C22.2, C23.1, C24.2, C25.1, CB1.1, CB1#2.1, CB1#3.1, CB1#4.1, CB1#5.1, CB1#6.1, CB1#7.1, CB1#8.1, CB1#9.1, CB1#10.1, CB1#11.1, CB1#12.1, CB1#13.1, CB1#14.1, CB1#15.1, CB1#16.1, CB1#17.1, CB1#18.1, CB1#19.1, CB1#20.1, CB1#21.1, CB1#22.1, CB1#23.1, CB1#24.1, CB1#25.1, CB1#26.1, CB1#27.1, CB1#28.1, CB1#29.1, CB1#30.1, D1.16 (GND), D2.16 (GND), D3.16 (GND), D4.16 (GND), D5.16 (GND), D6.16 (GND), D7.16 (GND), D8.16 (GND), D9.16 (GND), D10.16 (GND), D11.16 (GND), D12.16 (GND), D13.16 (GND), D14.16 (GND), D15.16 (GND), D16.16 (GND), D17.7 (GND), D17.23 (PB5), D18.1 (Vss), D18.24 (~A9), D19.12 (VSS), D19.20 (CKFS), D20.1 (Ea), D20.8 (GND), D20.15 (Eb), D21.1 (Ea), D21.8 (GND), D21.15 (Eb), D22.1 (Ea), D22.8 (GND), D22.13 (I3b), D22.15 (Eb), D23.1 (Ea), D23.3 (I3a), D23.8 (GND), D23.13 (I3b), D23.15 (Eb), D24.7 (~E), D24.8 (GND), D25.1 (GND), D26.1 (OEa), D26.5 (I1a), D26.6 (I0a), D26.8 (GND), D26.10 (I0b), D26.11 (I1b), D26.15 (OEb), D28.8 (GND), D28.14 (CS2), D29.7 (GND), D30.29 (GND), D31.14 (GND), D32.8 (GND), D33.12 (GND), D34.4 (GND), D35.7 (GND), D36.7 (GND), D37.8 (GND), D38.8 (GND), D38.15 (OE), D39.8 (GND), D40.7 (GND), D41.7 (GND), D42.7 (GND), D43.7 (GND), D44.7 (GND), D45.10 (GND), D46.10 (GND), D47.10 (GND), D48.10 (GND), D49.8 (GND), D50.8 (GND), D51.8 (GND), D52.1 (Ea), D52.8 (GND), D52.12 (I2b), D52.15 (Eb), D53.1 (Ea), D53.4 (I2a), D53.5 (I1a), D53.8 (GND), D53.15 (Eb), D54.8 (GND), D55.8 (GND), D56.8 (GND), D57.7 (GND), D58.10 (GND), D59.8 (GND), D60.12 (GND), D61.12 (GND), D62.12 (VSS), D65.12 (VSS), D65.18 (~EP), D65.19 (A10), D65.20 (~G), D66.7 (GND), D66.12 (D), D67.8 (GND), D67.13 (W), D67.14 (~CE), D68.8 (GND), D69.8 (GND), D69.15 (Q), D70.20 (GND), D71.7 (GND), D72.2 (R0(1)), D72.3 (R0(2)), D72.10 (GND), D73.7 (GND), D74.2 (Ea2), D74.8 (GND), D75.7 (GND), D76.7 (GND), D77.2 (D), D77.7 (GND), D78.7 (GND), D79.8 (GND), D80.8 (GND), D81.7 (~E), D81.8 (GND), D82.12 (GND), D83.12 (GND), D84.1 (OE), D84.10 (GND), D85.7 (GND), D86.4 (GND), D87.8 (GND), D87.11 (~Er), D88.8 (GND), D89.10 (GND), IC63.1 (CA), IC63.8 (VSS), IC63.9 (CB), IC64.1 (CA), IC64.8 (VSS), P2.1, P6.1, P8.1, R5.1, R14.1, R25.2, R27.1, R51.1, R65.2, R66.2, R102.1, R105.1, R128.1, R130.1, R133.1, VD1.2 (A), VD11.2 (A), VD14.2 (A), VT1.1 (E), VT3.1 (E), VT4.1 (E), VT5.1 (E), X1.A25, X1.B1, X2.2, X2.7, X2.S (К), X3.2, X3.S (К), X4.B1, X4.B2, X4.B3, X4.B4, X4.B5, X4.B6, X4.B7, X4.B8, X4.B9, X4.B10, X4.B11, X4.B12, X4.B13, X4.B14 (B14~), X4.B15, X4.B16, X4.B17, X5.A1.2, X5.A1.S (К), X5.B1.S (К), X6.S (К), X7.2, X7.S (К), X8.1, X9.12
unnamed: C1.1, D36.2, R1.2
unnamed: C1.2, D36.3, R2.1
unnamed: C2.1, D36.10, R3.2
unnamed: C2.2, D36.9, R4.1
unnamed: C3.2, IC63.7 (RA), IC63.15 (RB), IC64.7 (RA), R5.2, VD1.1 (K)
unnamed: C9.2, D19.22 (PS), R34.1
unnamed: C11.2, D19.2 (OSC1), Q3.2, R37.1
unnamed: C12.2, Q3.1, R38.1
unnamed: C14.1, DR1.2, VT2.3 (C)
unnamed: C18.2, D68.13 (D4), D71.6 (~Q)
unnamed: C26.1, DR2.2, VD10.2 (A), VT4.3 (C)
unnamed: C26.2, VD13.1 (K), VD14.1 (K)
unnamed: D19.3 (OSC2), R37.2, R38.2
unnamed: D19.13 (CE), R35.1, VT1.3 (C)
unnamed: D20.7 (Za), R39.1
unnamed: D20.9 (Zb), R40.1
unnamed: D21.7 (Za), R41.1
unnamed: D21.9 (Zb), R42.1
unnamed: D22.7 (Za), R43.1
unnamed: D22.9 (Zb), R44.1
unnamed: D23.7 (Za), R45.1
unnamed: D23.9 (Zb), R46.1
unnamed: D24.5 (Z), R24.1
unnamed: D25.23 (E), D41.11
unnamed: D29.11, D57.3 (C), D57.11 (C)
unnamed: D31.1 (A15), D35.11
unnamed: D31.27 (A14), D35.8
unnamed: D32.9 (Cp), D44.6
unnamed: D35.5, D44.8
unnamed: D36.1, Q1.2, R1.1
unnamed: D36.6, D43.3, D43.5
unnamed: D36.11, Q2.2, R3.1
unnamed: D38.4 (Za), D39.5 (P2)
unnamed: D39.4 (P1), D39.15 (Q0)
unnamed: D40.2 (D), D75.3
unnamed: D40.6 (~Q), D41.1, D41.4
unnamed: D40.12 (D), D44.3
unnamed: D41.3, R8.1
unnamed: D41.5, D42.8
unnamed: D41.6, R9.1
unnamed: D43.8, D66.8 (~Q)
unnamed: D43.9, D85.11
unnamed: D43.13, VD2.1 (K)
unnamed: D49.3 (P0), D77.9 (Q)
unnamed: D49.4 (P1), D77.8 (~Q)
unnamed: D50.12 (Q3), D51.2 (Dsr), D52.3 (I3a), D52.5 (I1a), D52.6 (I0a)
unnamed: D50.14 (Q1), D53.3 (I3a), D53.6 (I0a)
unnamed: D51.14 (Q1), D52.10 (I0b), D52.13 (I3b)
unnamed: D54.10 (Q1b), R134.2
unnamed: D59.2 (Q0), R57.2
unnamed: D59.5 (Q1), R56.2
unnamed: D59.7 (Q2), R55.2
unnamed: D59.10 (Q3), R54.2
unnamed: D59.12 (Q4), R53.2
unnamed: D59.15 (Q5), R52.2
unnamed: D65.1 (A7), IC63.10 (EB), IC64.6 (Q3A)
unnamed: D65.6 (A2), IC63.5 (Q2A)
unnamed: D65.7 (A1), IC63.4 (Q1A)
unnamed: D65.8 (A0), IC63.3 (Q0A)
unnamed: D65.23 (A8), IC63.11 (Q0B)
unnamed: D66.2 (D), D66.6 (~Q)
unnamed: D66.5 (Q), D66.11 (C)
unnamed: D66.9 (Q), D66.13 (~R), R15.1
unnamed: D68.2 (Q0), D69.10 (A0)
unnamed: D68.5 (Q1), D69.11 (A1)
unnamed: D68.7 (Q2), D69.12 (A2)
unnamed: D68.9 (Cp), D72.9 (Q1)
unnamed: D68.10 (Q3), D69.13 (A3), D73.1
unnamed: D68.12 (Q4), D69.14 (A4), D71.1 (~R)
unnamed: D68.14 (D5), D71.5 (Q)
unnamed: D70.4 (~CS), D74.7 (Q0a)
unnamed: D70.15 (~DACK), R76.1
unnamed: D70.17 (IDX), D73.10
unnamed: D70.25 (WE), D76.1
unnamed: D70.27 (HD), D76.13
unnamed: D70.28 (US1), D73.3
unnamed: D70.29 (US0), D73.5, D75.10
unnamed: D70.30 (WDA), D76.11
unnamed: D70.33 (FLT_TR0), D85.3
unnamed: D70.34 (WP_TS), D73.8
unnamed: D70.37 (FR_STP), D75.4
unnamed: D70.38 (LCT_DIR), D76.9
unnamed: D71.11 (C), D74.9 (Q0b)
unnamed: D72.14 (CP0), D73.2
unnamed: D73.4, D75.9
unnamed: D73.6, D76.5
unnamed: D73.12, D85.1
unnamed: D75.11, VD9.1 (K)
unnamed: D77.5 (Q), IC64.15 (RB)
unnamed: D78.3, D78.4
unnamed: D78.6, D84.11 (Cp)
unnamed: D82.17 (DB3), R83.1
unnamed: D82.18 (DB2), R82.1
unnamed: D83.17 (DB3), R87.1
unnamed: D83.18 (DB2), R86.1
unnamed: D83.19 (DB1), R85.1
unnamed: D83.20 (DB0), R84.1
unnamed: D85.6, R7.1
unnamed: D86.1 (S), R123.1
unnamed: D88.6 (Q4), VD12.1 (K)
unnamed: P7.1, P7#2.1, R33.2, VD6.2 (A)
unnamed: R16.2, VD3.1 (K)
unnamed: R36.2, VT1.2 (B)
unnamed: R52.1, R53.1, R59.2, R62.2
unnamed: R54.1, R55.1, R60.2, R63.2
unnamed: R56.1, R57.1, R61.2, R64.2
unnamed: R58.1, R59.1, R60.1, R61.1, VD8.2 (A), VT2.2 (B)
unnamed: R65.1, VT2.1 (E)
unnamed: R81.2, X2.1
unnamed: R101.2, VD15.1 (K)
unnamed: R102.2, VD16.1 (K)
unnamed: R114.2, X5.A1.1
unnamed: R115.2, X5.A1.3
unnamed: R116.2, X5.A1.4
unnamed: R117.2, X5.A1.5
unnamed: R118.2, X5.A1.7
unnamed: R119.2, X5.B1.1
unnamed: R120.2, X5.B1.3
unnamed: R121.2, X5.B1.4
unnamed: R122.2, X5.B1.5
unnamed: R127.1, R128.2, VT3.2 (B)
unnamed: R127.2, X7.4, X7.7
unnamed: R129.2, R130.2, VT4.2 (B)
unnamed: R131.2, R133.2, VT5.2 (B)
VCC: C20.1, C22.1, CB1.2, CB1#2.2, CB1#3.2, CB1#4.2, CB1#5.2, CB1#6.2, CB1#7.2, CB1#8.2, CB1#9.2, CB1#10.2, CB1#11.2, CB1#12.2, CB1#13.2, CB1#14.2, CB1#15.2, CB1#16.2, CB1#17.2, CB1#18.2, CB1#19.2, CB1#20.2, CB1#21.2, CB1#22.2, CB1#23.2, CB1#24.2, CB1#25.2, CB1#26.2, CB1#27.2, CB1#28.2, CB1#29.2, CB1#30.2, D1.8 (VCC), D2.8 (VCC), D3.8 (VCC), D4.8 (VCC), D5.8 (VCC), D6.8 (VCC), D7.8 (VCC), D8.8 (VCC), D9.8 (VCC), D10.8 (VCC), D11.8 (VCC), D12.8 (VCC), D13.8 (VCC), D14.8 (VCC), D15.8 (VCC), D16.8 (VCC), D17.26 (VCC), D18.25 (A8), D18.28 (BC2), D18.40 (Vcc), D20.16 (VCC), D21.16 (VCC), D22.16 (VCC), D23.16 (VCC), D24.16 (VCC), D25.20 (VCC), D26.16 (VCC), D28.16 (VCC), D29.14 (VCC), D30.11 (VCC), D31.28 (VCC), D32.16 (VCC), D33.11 (G0), D33.14 (G1), D33.22 (~RD), D33.24 (VCC), D34.26 (VCC), D35.14 (VCC), D36.14 (VCC), D37.1 (~MR), D37.7 (CEP), D37.9 (~PE), D37.10 (CET), D37.16 (VCC), D38.16 (VCC), D39.1 (Mr), D39.9 (S0), D39.10 (S1), D39.16 (VCC), D40.1 (~R), D40.13 (~R), D40.14 (VCC), D41.14 (VCC), D42.14 (VCC), D43.14 (VCC), D44.14 (VCC), D45.20 (VCC), D46.20 (VCC), D47.20 (VCC), D48.20 (VCC), D49.1 (Mr), D49.16 (VCC), D50.1 (Mr), D50.16 (VCC), D51.1 (Mr), D51.16 (VCC), D52.16 (VCC), D53.12 (I2b), D53.16 (VCC), D54.16 (VCC), D55.16 (VCC), D56.16 (VCC), D57.1 (~R), D57.4 (~S), D57.10 (~S), D57.13 (~R), D57.14 (VCC), D58.20 (VCC), D59.16 (VCC), D60.9 (~RA), D60.23 (~WB), D60.24 (VCC), D61.9 (~RA), D61.23 (~WB), D61.24 (VCC), D62.21 (VPP), D62.24 (VCC), D65.21 (VPP), D65.24 (VCC), D66.1 (~R), D66.14 (VCC), D67.16 (VCC), D68.1 (~Mr), D68.16 (VCC), D69.16 (VCC), D70.40 (Vcc), D71.4 (~S), D71.10 (~S), D71.13 (~R), D71.14 (VCC), D72.5 (VCC), D73.14 (VCC), D74.16 (VCC), D75.14 (VCC), D76.14 (VCC), D77.1 (~R), D77.10 (~S), D77.13 (~R), D77.14 (VCC), D78.1, D78.13, D78.14 (VCC), D79.1 (~Mr), D79.16 (VCC), D80.16 (VCC), D81.16 (VCC), D82.9 (~RA), D82.23 (~WB), D82.24 (VCC), D83.9 (~RA), D83.23 (~WB), D83.24 (VCC), D84.20 (VCC), D85.14 (VCC), D87.16 (VCC), D88.16 (VCC), D89.20 (VCC), DR1.1, DR2.1, IC63.16 (VDD), IC64.16 (VDD), P1.1, P5.1, R26.2, R58.2, R76.2, R123.2, R126.2, R132.1, RN1.1 (common), RN2.1 (common), RN3.1 (common), RN4.1 (R1.1), RN5.1 (R1.1), RN6.1 (R1.1), RN7.1 (R1.1), RN8.1 (R1.1), RN9.1 (common), VD3.2 (A), VD4.1, VD5.1 (K), VD7.2 (A), VD15.2 (A), VD16.2 (A), X1.A14, X5.B1.6, X5.B1.7
